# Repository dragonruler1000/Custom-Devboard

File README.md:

# Primortia Devboard
This is a custom rp2040 devboard that i wanted to make so i could use a custom board instead of a pico for a few projects and because i thought that it would be a fun challange and a way to test my knowlage of how to route a trace properly. sense it is PCBA the only parts that are soldered after it arrives is the pins on the edges.

BOM:
| Item Count | item name          | Unit price $ | Total Price* | Price with discounts* | Link                                                                     | Running total $* | Running total with coupons*    | part number | Notes |
|------------|--------------------|--------------|--------------|-----------------------|--------------------------------------------------------------------------|------------------|--------------------------------|-------------|-------|
| 2          | rp2040             | 0.98         | 1.96         | 1.96                  | https://jlcpcb.com/partdetail/RaspberryPi-RP2040/C2040                   | 2.08             | 2.08                           | 1           |       |
| 2          | USB-C port         | 0.18         | 0.36         | 0.36                  | https://jlcpcb.com/partdetail/Korean_HropartsElec-TYPE_C_31_M12/C165948  | 2.46             | 2.46                           | 2           |       |
| 2          | crystal oscillator | 0.07         | 0.14         | 0.14                  | https://jlcpcb.com/partdetail/YXC_CrystalOscillators-X322512MSB4SI/C9002 | 2.61             | 2.61                           | 3           |       |
| 2          | flash memory       | 0.69         | 1.38         | 1.38                  | https://jlcpcb.com/partdetail/3384470-IS25WP016D_JULETR/C2976734         | 4.07             | 4.07                           | 4           |       |
| 2          | bush button        | 0.06         | 0.12         | 0.12                  | https://jlcpcb.com/partdetail/XUNPU-TS_1088AR02016/C720477               | 4.2              | 4.2                            | 5           |       |
| 2          | Schottky diode     | 0.04         | 0.08         | 0.08                  | https://jlcpcb.com/partdetail/TECHPUBLIC-DMG1012T/C2830301               | 4.28             | 4.28                           | 6           |       |
| 2          | LDO                | 0.63         | 1.26         | 1.26                  | https://jlcpcb.com/partdetail/MicrochipTech-MCP1700T_1202ETT/C144202     | 5.62             | 5.62                           | 7           |       |
| 4          | 1uF capacitor      | 0.01         | 0.04         | 0.04                  | https://jlcpcb.com/partdetail/53938-CL05A105KA5NQNC/C52923               | 5.66             | 5.66                           | 8           |       |
| 22         | 0.1uf capacitor    | 0.01         | 0.22         | 0.22                  | https://jlcpcb.com/partdetail/1877-CL05B104KO5NNNC/C1525                 | 5.89             | 5.89                           | 9           |       |
| 4          | 33pF capacitors    | 0.01         | 0.04         | 0.04                  | https://jlcpcb.com/partdetail/1914-0402CG330J500NT/C1562                 | 5.93             | 5.93                           | 10          |       |
| 2          | 1nF Capacitor      | 0.01         | 0.02         | 0.02                  | https://jlcpcb.com/partdetail/1875-0402B102K500NT/C1523                  | 5.95             | 5.95                           | 10          |       |
| 4          | 10uF Capacitors    | 0.01         | 0.04         | 0.04                  | https://jlcpcb.com/partdetail/20411-CL10A106KP8NNNC/C19702               | 5.99             | 5.99                           | 10          |       |
| 2          | LED                | 0.01         | 0.02         | 0.02                  | https://jlcpcb.com/partdetail/CHONGTIAN-CT_1608UGCP4/C52675989           | 6.01             | 6.01                           | 10          |       |
| 2          | 470R Resistors     | 0.01         | 0.02         | 0.02                  | https://jlcpcb.com/partdetail/25860-0402WGF4700TCE/C25117                | 6.03             | 6.03                           | 8           |       |
| 4          | 5.1k Resistors     | 0.01         | 0.04         | 0.04                  | https://jlcpcb.com/partdetail/26648-0402WGF5101TCE/C25905                | 6.07             | 6.07                           | 9           |       |
| 4          | 1k Resistors       | 0.01         | 0.04         | 0.04                  | https://jlcpcb.com/partdetail/12256-0402WGF1001TCE/C11702                | 6.11             | 6.11                           | 10          |       |
| 4          | 27 Resistors       | 0.01         | 0.04         | 0.04                  | https://jlcpcb.com/partdetail/Sunway-SC0402J27R0F2ANRH/C5141043          | 6.15             | 6.15                           | 8           |       |
| 2          | 10K Resistors      | 0.01         | 0.02         | 0.02                  | https://jlcpcb.com/partdetail/26487-0402WGF1002TCE/C25744                | 6.17             | 6.17                           | 9           |       |
| 2          | 100K Resistors     | 0.01         | 0.02         | 0.02                  | https://jlcpcb.com/partdetail/26484-0402WGF1003TCE/C25741                | 6.19             | 6.19                           | 10          |       |
| 2          | 200K Resistors     | 0.01         | 0.02         | 0.02                  | https://jlcpcb.com/partdetail/26507-0402WGF2003TCE/C25764                | 6.21             | 6.21                           | 10          |       |
| 4          | 1x20 pin header    | 1.04         | 4.16         | 4.16                  | https://www.digikey.com/en/products/detail/adam-tech/PH1-20-UA/9830398   | 10.62            | 10.62                          | 12          |       |
| 1          | PCB                | 3.1          | 3.1          | 3.1                   | https://jlcpcb.com/partdetail/CHONGTIAN-CT_1608UGCP4/C52675989           | 13.91            | 13.91                          | 10          |       |
| 1          | PCBA – parts price | 33.65        | 33.65        | 33.65                 | https://jlcpcb.com/                                                      | 49.58            | 49.58                          | 10          |       |
| 1          | JLCPCB Shipping    | 7.29         | 7.29         | 3                     | https://jlcpcb.com/                                                      | 57.31            | 52.76                          | 10          |       |
| 1          | Digikey Shipping   | 6.99         | 6.99         | 6.99                  | https://www.digikey.com                                                  | 64.72            | 60.17                          | 10          |       |
|            |                    |              |              |                       |                                                                          |                  |                                |             |       |
|            |                    |              |              |                       |                                                                          |                  | *Rounded to two decimal places |             |       |

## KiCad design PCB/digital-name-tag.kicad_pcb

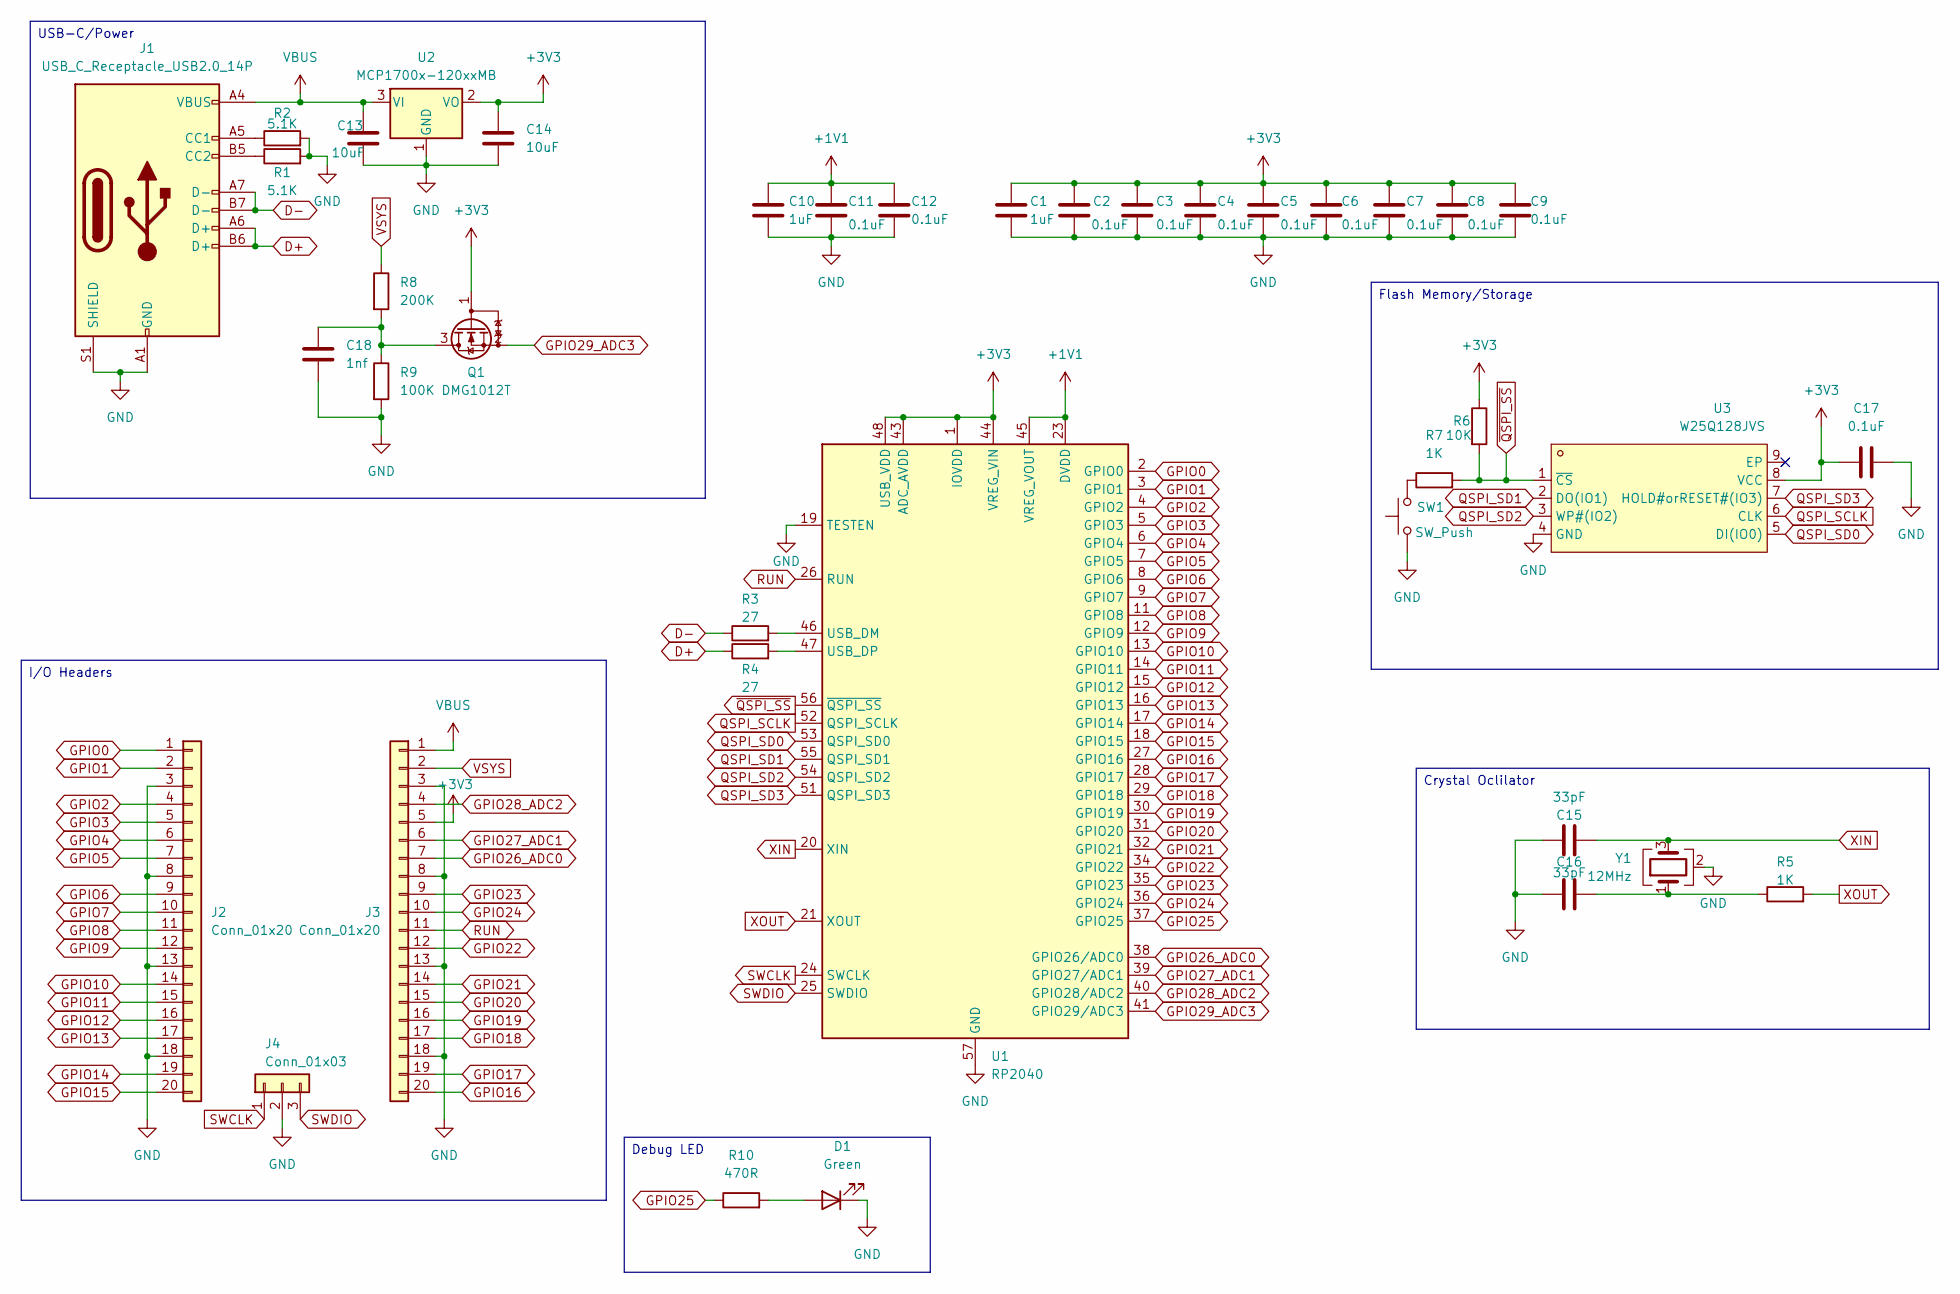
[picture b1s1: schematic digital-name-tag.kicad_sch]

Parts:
C1, C10: 1uF; C_0402_1005Metric
C2, C3, C4, C5, C6, C7, C8, C9, C11, C12, C17: 0.1uF; C_0402_1005Metric
C13, C14: 10uF; C_0603_1608Metric
C15, C16: 33pF; C_0402_1005Metric; lcsc part # C1663
C18: 1nf; C_0402_1005Metric
D1: Green; LED_0603_1608Metric
J1: USB_C_Receptacle_USB2.0_14P; USB_C_Receptacle_HRO_TYPE-C-31-M-12
J2, J3: Conn_01x20; PinHeader_1x20_P2.54mm_Vertical
J4: Conn_01x03; PinHeader_1x03_P2.54mm_Vertical
Q1: DMG1012T; SOT-523
R1, R2: 5.1K; R_0402_1005Metric
R3, R4: 27; R_0402_1005Metric
R5, R7: 1K; R_0402_1005Metric
R6: 10K; R_0402_1005Metric
R8: 200K; R_0402_1005Metric; lcsc part # C22369193
R9: 100K; R_0402_1005Metric
R10: 470R; R_0402_1005Metric
SW1: SW_Push; SW_Push_SPST_NO_Alps_SKRK
U1: RP2040; QFN-56-1EP_7x7mm_P0.4mm_EP3.2x3.2mm
U2: MCP1700x-120xxMB; SOT-23
U3: W25Q128JVS; USON-8_L3.0-W2.0-P0.50-BL-EP; MPN W25Q16JVUXIQ; LCSC Part C2843335
Y1: 12MHz; Crystal_SMD_3225-4Pin_3.2x2.5mm; lcsc part # C9002

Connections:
+1V1: C10.1, C11.1, C12.1, U1.23 (DVDD), U1.45 (VREG_VOUT), U1.50 (DVDD)
+3V3: C1.1, C2.1, C3.1, C4.1, C5.1, C6.1, C7.1, C8.1, C9.1, C14.1, C17.1, J3.5, Q1.1 (G), R6.1, U1.1 (IOVDD), U1.10 (IOVDD), U1.22 (IOVDD), U1.33 (IOVDD), U1.42 (IOVDD), U1.43 (ADC_AVDD), U1.44 (VREG_VIN), U1.48 (USB_VDD), U1.49 (IOVDD), U2.2 (VO), U3.8 (VCC)
D+: J1.A6 (D+), J1.B6 (D+), R4.1
D-: J1.A7 (D-), J1.B7 (D-), R3.1
GND: C1.2, C2.2, C3.2, C4.2, C5.2, C6.2, C7.2, C8.2, C9.2, C10.2, C11.2, C12.2, C13.2, C14.2, C15.1, C16.1, C17.2, C18.2, D1.1 (K), J1.A1 (GND), J1.A12 (GND), J1.B1 (GND), J1.B12 (GND), J1.S1 (SHIELD), J2.3, J2.8, J2.13, J2.18, J3.3, J3.8, J3.13, J3.18, J4.2, R1.2, R2.2, R9.2, SW1.1, U1.19 (TESTEN), U1.57 (GND), U2.1 (GND), U3.4 (GND), Y1.2 (G), Y1.4 (G)
GPIO0: J2.1, U1.2 (GPIO0)
GPIO1: J2.2, U1.3 (GPIO1)
GPIO2: J2.4, U1.4 (GPIO2)
GPIO3: J2.5, U1.5 (GPIO3)
GPIO4: J2.6, U1.6 (GPIO4)
GPIO5: J2.7, U1.7 (GPIO5)
GPIO6: J2.9, U1.8 (GPIO6)
GPIO7: J2.10, U1.9 (GPIO7)
GPIO8: J2.11, U1.11 (GPIO8)
GPIO9: J2.12, U1.12 (GPIO9)
GPIO10: J2.14, U1.13 (GPIO10)
GPIO11: J2.15, U1.14 (GPIO11)
GPIO12: J2.16, U1.15 (GPIO12)
GPIO13: J2.17, U1.16 (GPIO13)
GPIO14: J2.19, U1.17 (GPIO14)
GPIO15: J2.20, U1.18 (GPIO15)
GPIO16: J3.20, U1.27 (GPIO16)
GPIO17: J3.19, U1.28 (GPIO17)
GPIO18: J3.17, U1.29 (GPIO18)
GPIO19: J3.16, U1.30 (GPIO19)
GPIO20: J3.15, U1.31 (GPIO20)
GPIO21: J3.14, U1.32 (GPIO21)
GPIO22: J3.12, U1.34 (GPIO22)
GPIO23: J3.9, U1.35 (GPIO23)
GPIO24: J3.10, U1.36 (GPIO24)
GPIO25: R10.1, U1.37 (GPIO25)
GPIO26_ADC0: J3.7, U1.38 (GPIO26/ADC0)
GPIO27_ADC1: J3.6, U1.39 (GPIO27/ADC1)
GPIO28_ADC2: J3.4, U1.40 (GPIO28/ADC2)
GPIO29_ADC3: Q1.2 (S), U1.41 (GPIO29/ADC3)
unnamed: C16.2, R5.1, Y1.1
unnamed: D1.2 (A), R10.2
unnamed: J1.A5 (CC1), R2.1
unnamed: J1.B5 (CC2), R1.1
unnamed: C18.1, Q1.3 (D), R8.2, R9.1
unnamed: R7.1, SW1.2
unnamed: R3.2, U1.46 (USB_DM)
unnamed: R4.2, U1.47 (USB_DP)
QSPI_SCLK: U1.52 (QSPI_SCLK), U3.6 (CLK)
QSPI_SD0: U1.53 (QSPI_SD0), U3.5 (DI(IO0))
QSPI_SD1: U1.55 (QSPI_SD1), U3.2 (DO(IO1))
QSPI_SD2: U1.54 (QSPI_SD2), U3.3 (WP#(IO2))
QSPI_SD3: U1.51 (QSPI_SD3), U3.7 (HOLD#orRESET#(IO3))
RUN: J3.11, U1.26 (RUN)
SWCLK: J4.1, U1.24 (SWCLK)
SWDIO: J4.3, U1.25 (SWDIO)
VBUS: C13.1, J1.A4 (VBUS), J1.A9 (VBUS), J1.B4 (VBUS), J1.B9 (VBUS), J3.1, U2.3 (VI)
VSYS: J3.2, R8.1
XIN: C15.2, U1.20 (XIN), Y1.3
XOUT: R5.2, U1.21 (XOUT)
~QSPI_SS: R6.2, R7.2, U1.56 (~QSPI_SS), U3.1 (~CS)

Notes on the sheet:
Flash Memory/Storage
USB-C/Power
Debug LED
Crystal Oclilator
I/O Headers

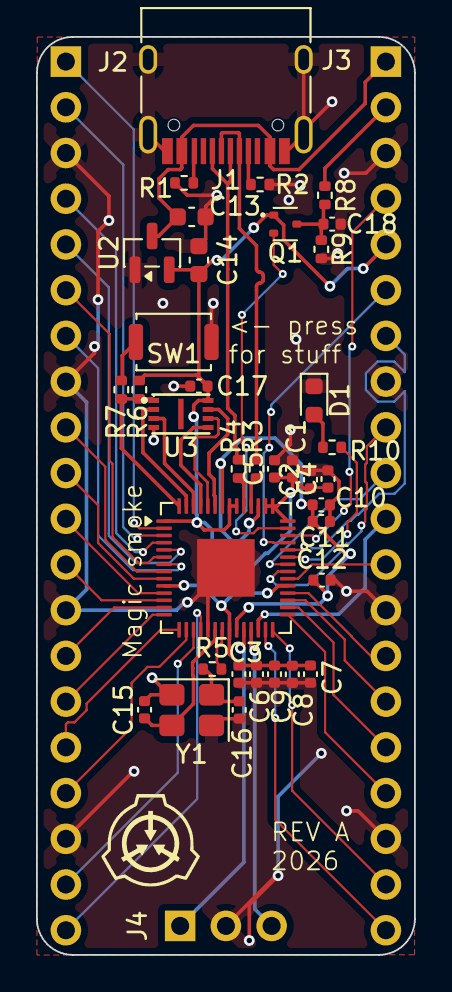
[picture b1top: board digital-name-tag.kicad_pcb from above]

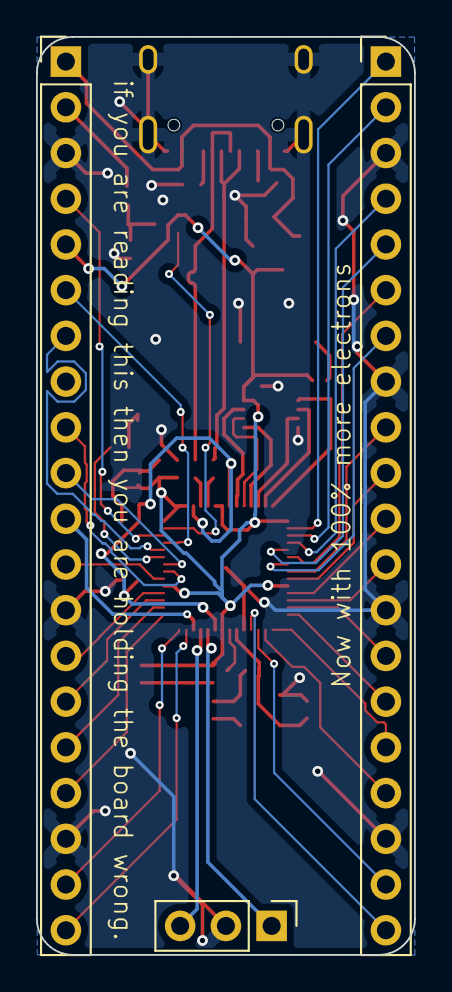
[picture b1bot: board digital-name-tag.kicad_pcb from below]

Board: 2 copper layers, 21.0 x 51.0 mm, 39 parts (3 on the bottom side), 56 nets.

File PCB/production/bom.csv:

Designator,Footprint,Quantity,Value,LCSC Part #
"C1, C10",0402,2,1uF,
"C11, C12, C17, C2, C3, C4, C5, C6, C7, C8, C9",0402,11,0.1uF,
"C13, C14",0603,2,10uF,
"C15, C16",0402,2,33pF,
C18,0402,1,1nf,
D1,0603,1,Green,
J1,USB_C_Receptacle_HRO_TYPE-C-31-M-12,1,USB_C_Receptacle_USB2.0_14P,
"J2, J3",PinHeader_1x20_P2.54mm_Vertical,2,Conn_01x20,
J4,PinHeader_1x03_P2.54mm_Vertical,1,Conn_01x03,
Q1,SOT-523,1,DMG1012T,
"R1, R2",0402,2,5.1K,
R10,0402,1,470R,
"R3, R4",0402,2,27,
"R5, R7",0402,2,1K,
R6,0402,1,10K,
R8,0402,1,200K,
R9,0402,1,100K,
SW1,SW_Push_SPST_NO_Alps_SKRK,1,SW_Push,
U1,QFN-56-1EP_7x7mm_P0.4mm_EP3.2x3.2mm,1,RP2040,
U2,SOT-23,1,MCP1700x-120xxMB,
U3,USON-8_L3.0-W2.0-P0.50-BL-EP,1,W25Q128JVS,C2843335
Y1,Crystal_SMD_3225-4Pin_3.2x2.5mm,1,12MHz,

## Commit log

2026-05-06 started on project
2026-05-06 wrote journal entry for latest sesion
2026-05-06 finished seting up the schematic and assigned all the footprints
2026-05-08 startet placing footpints and updated limage links for JOURNAL.md
2026-05-08 Fix image paths in JOURNAL.md
    Updated image paths in the journal entries to use relative paths.
2026-05-14 finnished layout and mostly got routing done
2026-05-14 added new journal entry
2026-05-15 fixed DRC errors
2026-05-15 put togeather BOM
2026-05-16 fixed BOM and got the pcb added to cart I think i forgot to save the BOM last time but i ended up changing a good portion of it anyways to change from exstended pcba to basic.
2026-05-16 fixed caplisation issue
2026-05-22 fileted the corners.
2026-05-22 maybe
2026-05-22 added silkscreen art
2026-05-25 updated gerbers
2026-06-03 Fix 3D model image filename in README
    Corrected the filename for the 3D model front image in the README.
2026-06-24 updated the schematic and pcb to have the correct power rails.
2026-06-26 made the production files
